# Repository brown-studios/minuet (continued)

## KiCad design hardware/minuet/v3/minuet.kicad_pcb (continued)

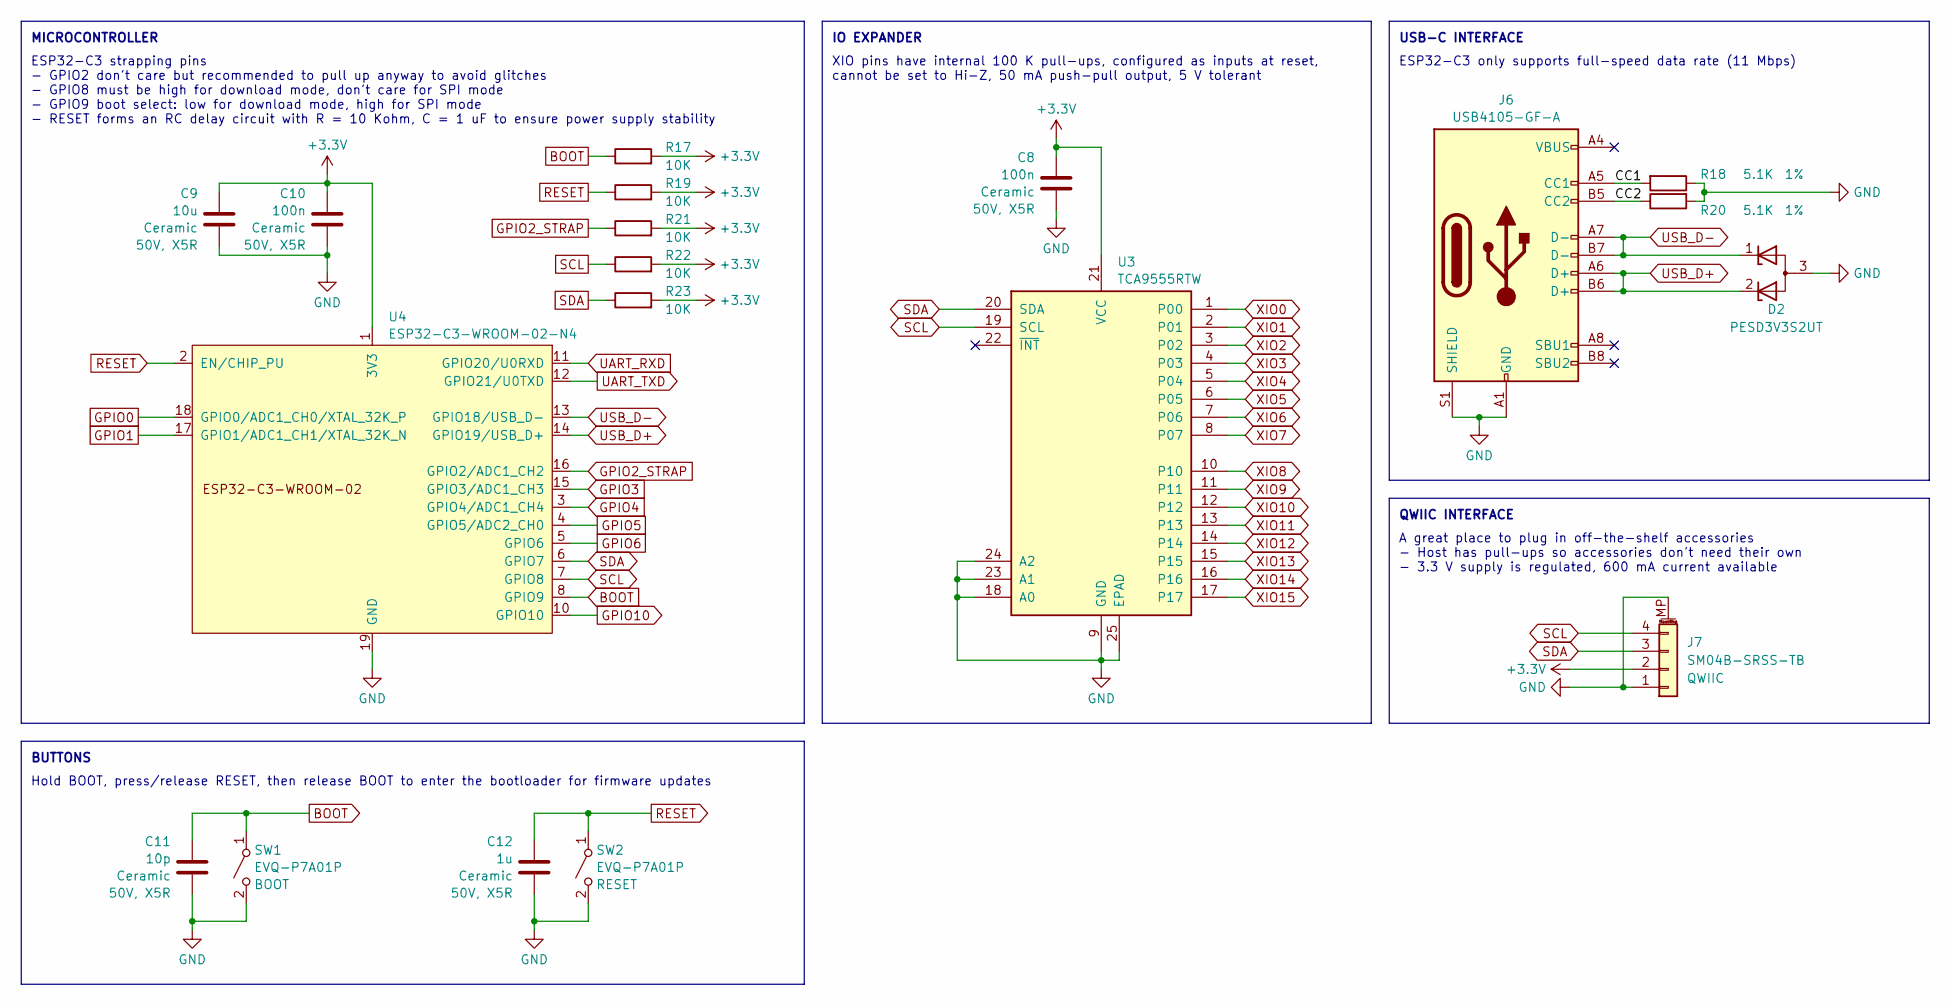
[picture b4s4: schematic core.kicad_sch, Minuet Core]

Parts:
C8, C10: 100n; C_0603_1608Metric; Rating 50V, X5R; LCSC C14663
C9: 10u; C_0805_2012Metric; Rating 50V, X5R; LCSC C15850
C11: 10p; C_0603_1608Metric; Rating 50V, X5R; LCSC C1634
C12: 1u; C_0603_1608Metric; Rating 50V, X5R; LCSC C15849
D2: PESD3V3S2UT; SOT-23; LCSC C84276
J6: USB4105-GF-A; USB_C_Receptacle_GCT_USB4105-xx-A_16P_TopMnt_Horizontal; LCSC C2988369
J7: SM04B-SRSS-TB; JST_SH_SM04B-SRSS-TB_1x04-1MP_P1.00mm_Horizontal; LCSC C160404
R17, R19, R21, R22, R23: 10K; R_0603_1608Metric; LCSC C25804
R18, R20: 5.1K; R_0603_1608Metric; Rating 1%; LCSC C23186
SW1, SW2: EVQ-P7A01P; SW_SPST_EVQP7A; LCSC C79167
U3: TCA9555RTW; WQFN-24-1EP_4x4mm_P0.5mm_EP2.45x2.45mm; LCSC C140277
U4: ESP32-C3-WROOM-02-N4; ESP32-C3-WROOM-02; LCSC C2934560

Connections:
+3.3V: C8.1, C9.2, C10.1, J7.2, R17.2, R19.2, R21.2, R22.2, R23.2, U3.21 (VCC), U4.1 (3V3); also elsewhere on the board
/core/CC1: J6.A5 (CC1), R18.2
/core/CC2: J6.B5 (CC2), R20.1
BOOT: C11.1, R17.1, SW1.1 (A), U4.8 (GPIO9); also elsewhere on the board
GND: C8.2, C9.1, C10.2, C11.2, C12.2, D2.3 (A), J6.A1 (GND), J6.A12 (GND), J6.B1 (GND), J6.B12 (GND), J6.S1 (SHIELD), J7.1, J7.MP (MountPin), R18.1, R20.2, SW1.2 (B), SW2.2 (B), U3.9 (GND), U3.18 (A0), U3.23 (A1), U3.24 (A2), U3.25 (EPAD), U4.9 (GND), U4.19 (GND); also elsewhere on the board
GPIO0: U4.18 (GPIO0/ADC1_CH0/XTAL_32K_P); also elsewhere on the board
GPIO1: U4.17 (GPIO1/ADC1_CH1/XTAL_32K_N); also elsewhere on the board
GPIO2_STRAP: R21.1, U4.16 (GPIO2/ADC1_CH2); also elsewhere on the board
GPIO3: U4.15 (GPIO3/ADC1_CH3); also elsewhere on the board
GPIO4: U4.3 (GPIO4/ADC1_CH4); also elsewhere on the board
GPIO5: U4.4 (GPIO5/ADC2_CH0); also elsewhere on the board
GPIO6: U4.5 (GPIO6); also elsewhere on the board
GPIO10: U4.10 (GPIO10); also elsewhere on the board
RESET: C12.1, R19.1, SW2.1 (A), U4.2 (EN/CHIP_PU); also elsewhere on the board
SCL: J7.4, R22.1, U3.19 (SCL), U4.7 (GPIO8); also elsewhere on the board
SDA: J7.3, R23.1, U3.20 (SDA), U4.6 (GPIO7); also elsewhere on the board
UART_RXD: U4.11 (GPIO20/U0RXD); also elsewhere on the board
UART_TXD: U4.12 (GPIO21/U0TXD); also elsewhere on the board
USB_D+: D2.2 (K), J6.A6 (D+), J6.B6 (D+), U4.14 (GPIO19/USB_D+)
USB_D-: D2.1 (K), J6.A7 (D-), J6.B7 (D-), U4.13 (GPIO18/USB_D-)
XIO0: U3.1 (P00); also elsewhere on the board
XIO1: U3.2 (P01); also elsewhere on the board
XIO2: U3.3 (P02); also elsewhere on the board
XIO3: U3.4 (P03); also elsewhere on the board
XIO4: U3.5 (P04); also elsewhere on the board
XIO5: U3.6 (P05); also elsewhere on the board
XIO6: U3.7 (P06); also elsewhere on the board
XIO7: U3.8 (P07); also elsewhere on the board
XIO8: U3.10; also elsewhere on the board
XIO9: U3.11; also elsewhere on the board
XIO10: U3.12; also elsewhere on the board
XIO11: U3.13; also elsewhere on the board
XIO12: U3.14; also elsewhere on the board
XIO13: U3.15; also elsewhere on the board
XIO14: U3.16; also elsewhere on the board
XIO15: U3.17; also elsewhere on the board

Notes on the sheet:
IO EXPANDER
USB-C INTERFACE
XIO pins have internal 100 K pull-ups, configured as inputs at reset, cannot be set to Hi-Z, 50 mA push-pull output, 5 V tolerant
ESP32-C3 strapping pins - GPIO2 don't care but recommended to pull up anyway to avoid glitches - GPIO8 must be high for download mode, don't care for SPI mode - GPIO9 boot select: low for download mode, high for SPI mode - RESET forms an RC delay circuit with R = 10 Kohm, C = 1 uF to ensure power s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
Hold BOOT, press/release RESET, then release BOOT to enter the bootloader for firmware updates
BUTTONS
ESP32-C3 only supports full-speed data rate (11 Mbps)
QWIIC INTERFACE
A great place to plug in off-the-shelf accessories - Host has pull-ups so accessories don't need their own - 3.3 V supply is regulated, 600 mA current available
MICROCONTROLLER

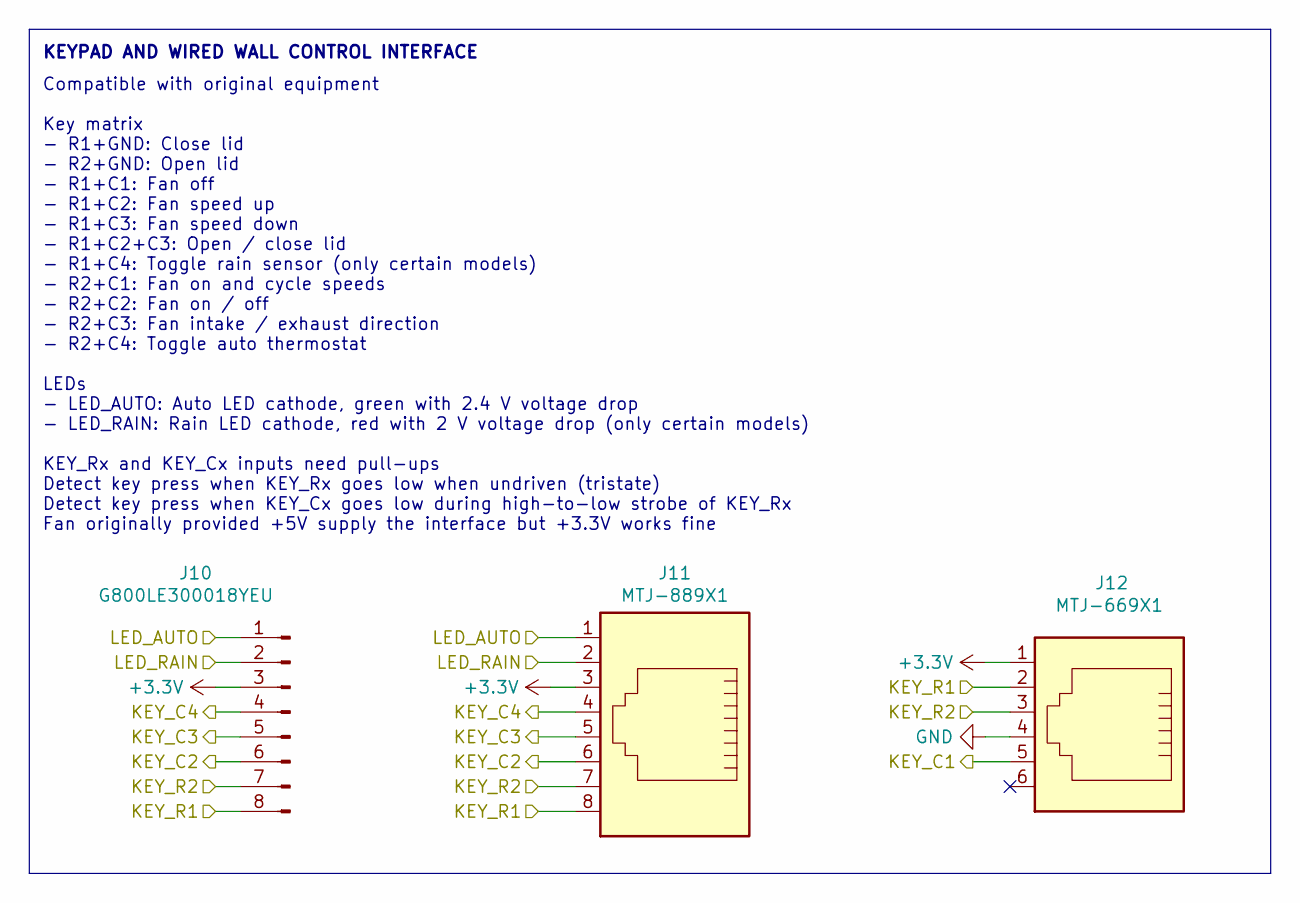
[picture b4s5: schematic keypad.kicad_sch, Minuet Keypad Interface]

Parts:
J10: G800LE300018YEU; PinHeader_1x08_P2.54mm_Vertical; LCSC C3345591
J11: MTJ-889X1; CONN_MTJ-889X1_ADM; LCSC C6105889
J12: MTJ-669X1; CONN_MTJ-669X1_ADM; LCSC C5785037

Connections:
+3.3V: J10.3, J11.3, J12.1; also elsewhere on the board
/keypad/LED_AUTO: J10.1, J11.1; also elsewhere on the board
/keypad/LED_RAIN: J10.2, J11.2; also elsewhere on the board
GND: J12.4; also elsewhere on the board
XIO2: J10.5, J11.5; also elsewhere on the board
XIO3: J10.7, J11.7, J12.3; also elsewhere on the board
XIO4: J10.6, J11.6; also elsewhere on the board
XIO5: J10.8, J11.8, J12.2; also elsewhere on the board
XIO6: J10.4, J11.4; also elsewhere on the board
XIO7: J12.5; also elsewhere on the board

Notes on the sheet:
Compatible with original equipment Key matrix - R1+GND: Close lid - R2+GND: Open lid - R1+C1: Fan off - R1+C2: Fan speed up - R1+C3: Fan speed down - R1+C2+C3: Open / close lid - R1+C4: Toggle rain sensor (only certain models) - R2+C1: Fan on and cycle speeds - R2+C2: Fan on / off - R2+C3: Fan inta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
KEYPAD AND WIRED WALL CONTROL INTERFACE

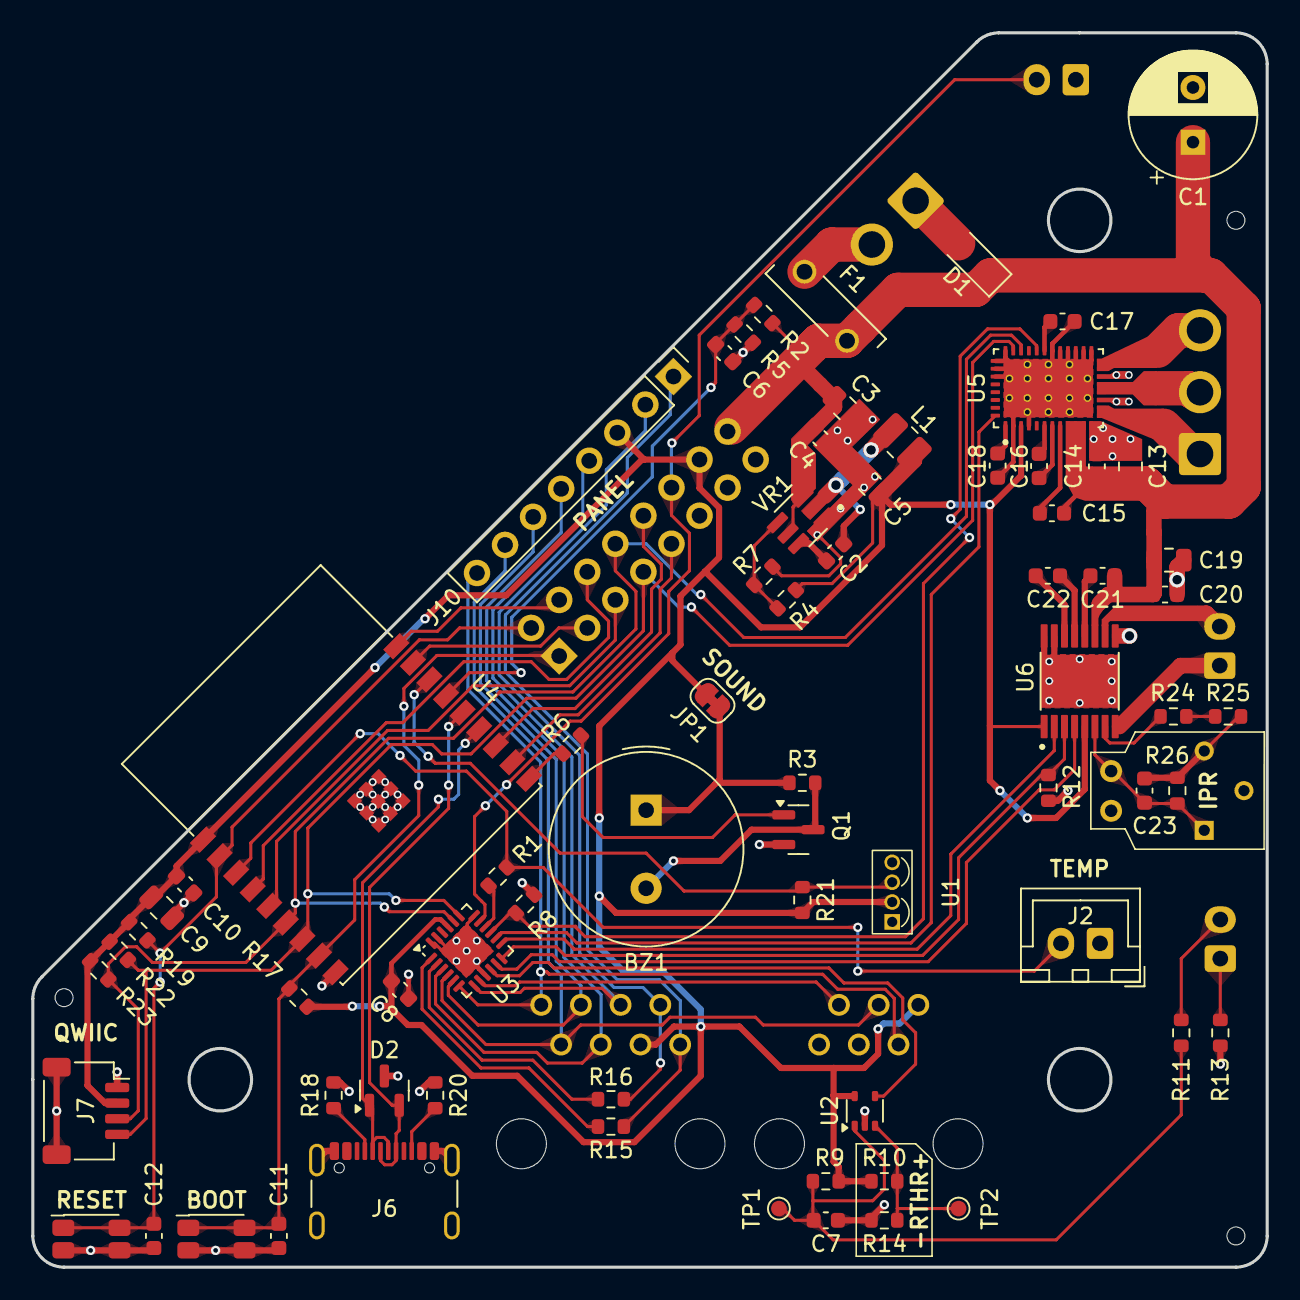
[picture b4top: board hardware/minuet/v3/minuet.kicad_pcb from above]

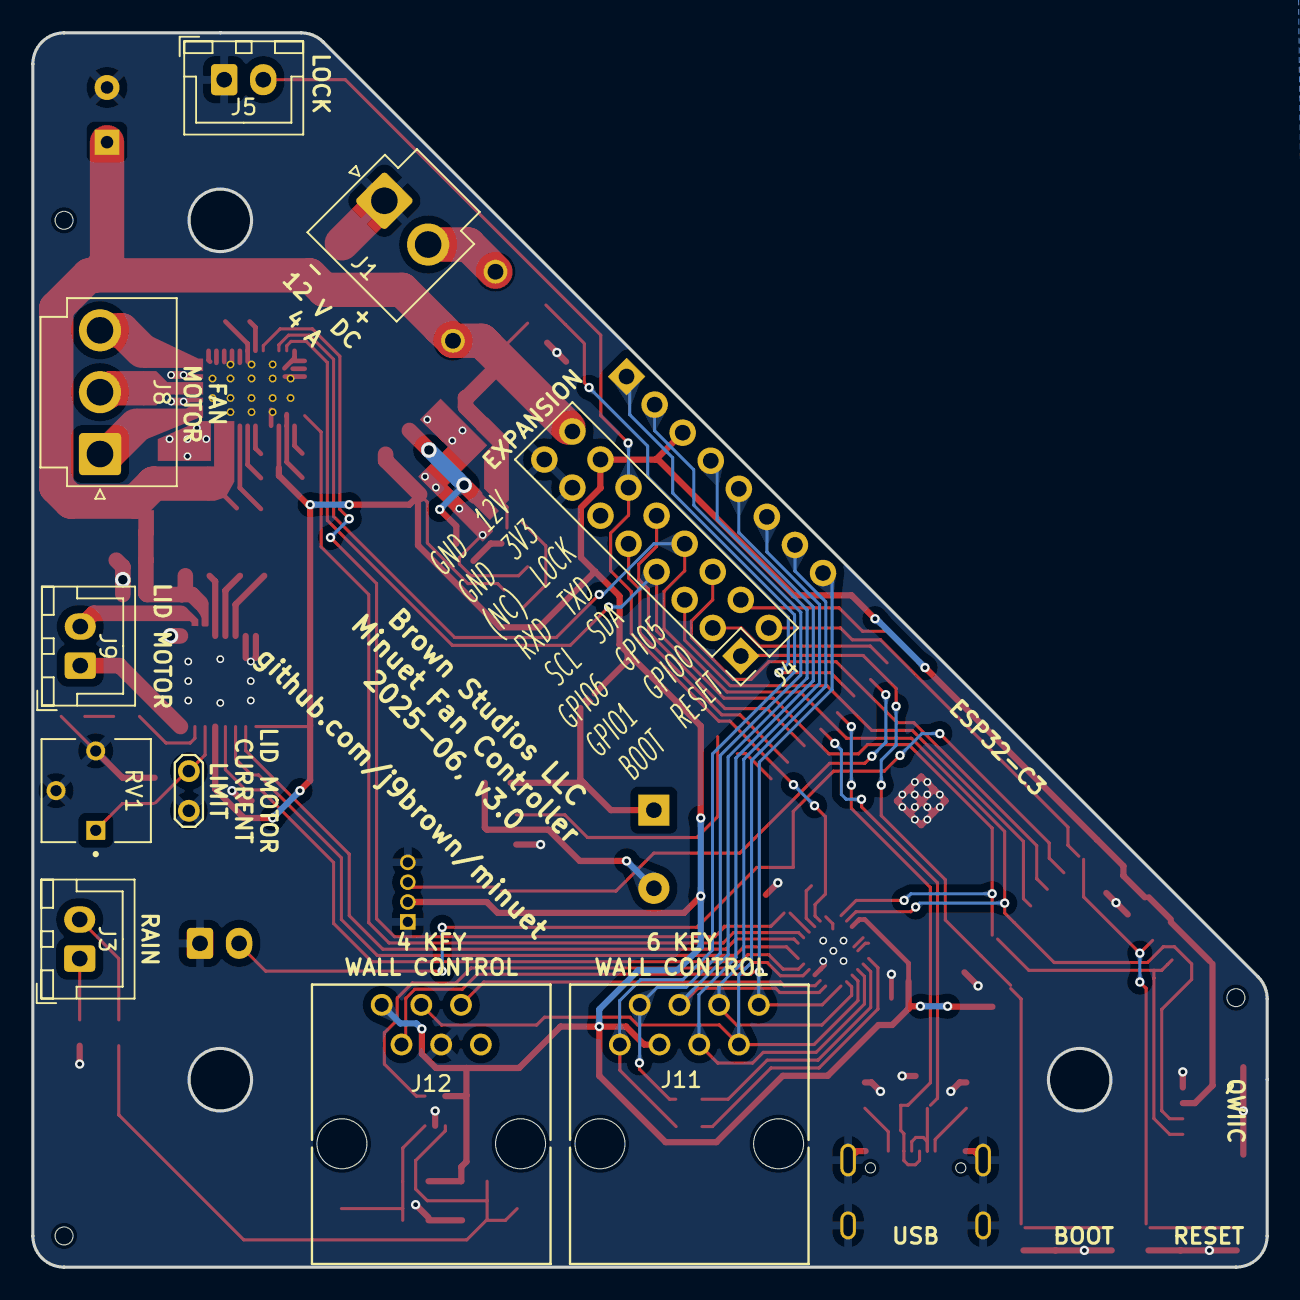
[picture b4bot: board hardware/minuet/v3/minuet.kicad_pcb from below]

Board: 2 copper layers, 79.0 x 79.0 mm, 88 parts (10 on the bottom side), 70 nets.

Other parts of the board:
TH1, TH2, TH3: JLCPCB_PCBA_Tooling_Hole

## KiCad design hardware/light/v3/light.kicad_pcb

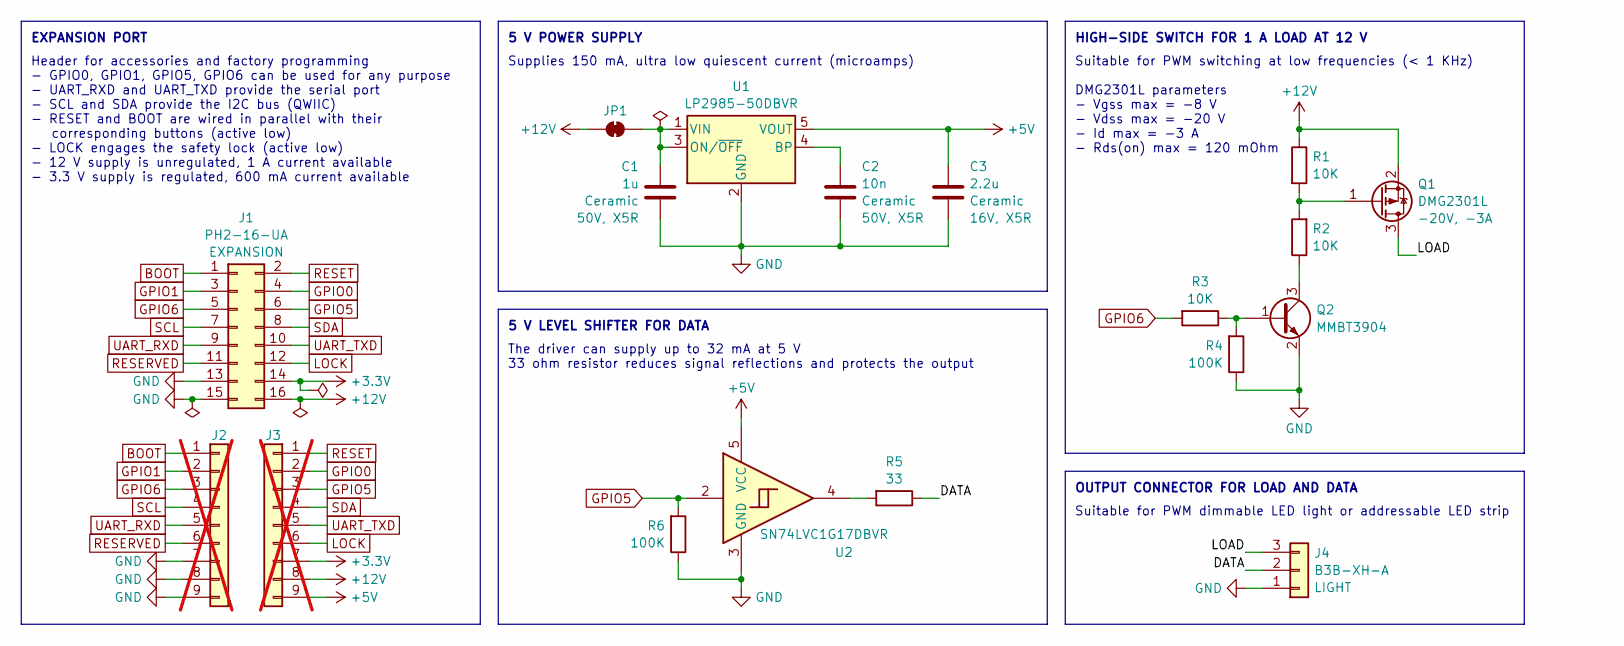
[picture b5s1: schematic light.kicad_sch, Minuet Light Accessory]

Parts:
C1: 1u; C_0603_1608Metric; Rating 50V, X5R; LCSC C15849
C2: 10n; C_0603_1608Metric; Rating 50V, X5R; LCSC C57112
C3: 2.2u; C_0603_1608Metric; Rating 16V, X5R; LCSC C23630
J1: PH2-16-UA; PinHeader_2x08_P2.54mm_Vertical; LCSC C492425
J2, J3: Conn_01x09; Pins_1x09; not fitted
J4: B3B-XH-A; JST_XH_B3B-XH-A_1x03_P2.50mm_Vertical; LCSC C144394
JP1: SolderJumper_2_Open; SolderJumper-2_P1.3mm_Bridged_RoundedPad1.0x1.5mm
Q1: DMG2301L; SOT-23; Rating -20V, -3A; LCSC C102619
Q2: MMBT3904; SOT-23; LCSC C20526
R1, R2, R3: 10K; R_0603_1608Metric; LCSC C25804
R4, R6: 100K; R_0603_1608Metric; LCSC C25803
R5: 33; R_0603_1608Metric; LCSC C23140
U1: LP2985-50DBVR; SOT-23-5; LCSC C74511
U2: SN74LVC1G17DBVR; SOT-23-5; LCSC C7836

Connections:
+3.3V: J1.14, J3.7
+5V: C3.2, J3.9, U1.5 (VOUT), U2.5 (VCC)
+12V: J1.16, J3.8, JP1.2 (B), Q1.2 (S), R1.1
/DATA: J4.2, R5.1
/LOAD: J4.3, Q1.3 (D)
BOOT: J1.1, J2.1
GND: C1.2, C2.1, C3.1, J1.13, J1.15, J2.7, J2.8, J2.9, J4.1, Q2.2 (E), R4.1, R6.1, U1.2 (GND), U2.3 (GND)
GPIO0: J1.4, J3.2
GPIO1: J1.3, J2.2
GPIO5: J1.6, J3.3, R6.2, U2.2
GPIO6: J1.5, J2.3, R3.2
LOCK: J1.12, J3.6
unnamed: C1.1, JP1.1 (A), U1.1 (VIN), U1.3 (ON/~OFF)
unnamed: Q1.1 (G), R1.2, R2.2
unnamed: Q2.1 (B), R3.1, R4.2
unnamed: Q2.3 (C), R2.1
unnamed: R5.2, U2.4
unnamed: C2.2, U1.4 (BP)
RESERVED: J1.11, J2.6
RESET: J1.2, J3.1
SCL: J1.7, J2.4
SDA: J1.8, J3.4
UART_RXD: J1.9, J2.5
UART_TXD: J1.10, J3.5

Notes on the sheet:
HIGH-SIDE SWITCH FOR 1 A LOAD AT 12 V
Suitable for PWM switching at low frequencies (< 1 KHz) DMG2301L parameters - Vgss max = -8 V - Vdss max = -20 V - Id max = -3 A - Rds(on) max = 120 mOhm
The driver can supply up to 32 mA at 5 V 33 ohm resistor reduces signal reflections and protects the output
5 V LEVEL SHIFTER FOR DATA
EXPANSION PORT
Header for accessories and factory programming - GPIO0, GPIO1, GPIO5, GPIO6 can be used for any purpose - UART_RXD and UART_TXD provide the serial port - SCL and SDA provide the I2C bus (QWIIC) - RESET and BOOT are wired in parallel with their corresponding buttons (active low) - LOCK engages the s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
Suitable for PWM dimmable LED light or addressable LED strip
Supplies 150 mA, ultra low quiescent current (microamps)
5 V POWER SUPPLY
OUTPUT CONNECTOR FOR LOAD AND DATA

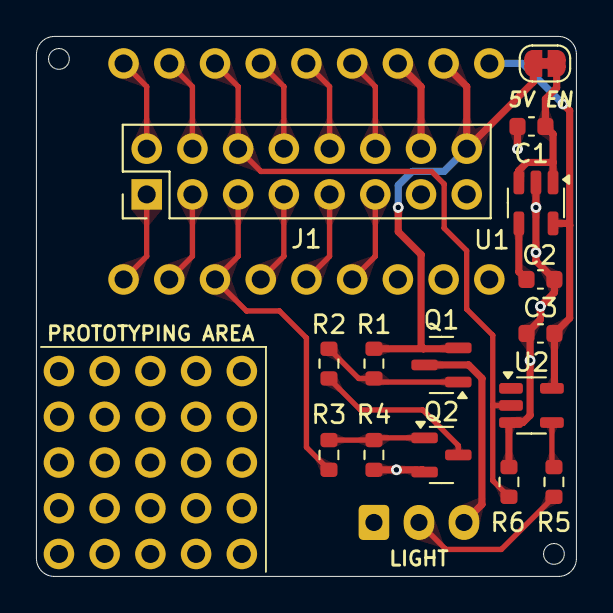
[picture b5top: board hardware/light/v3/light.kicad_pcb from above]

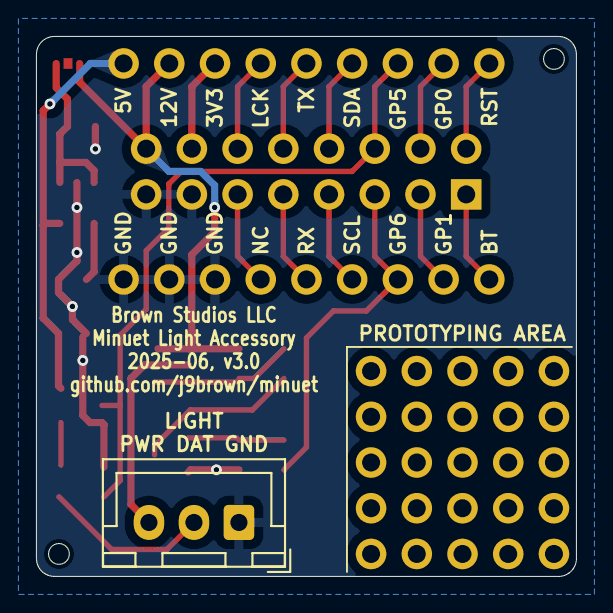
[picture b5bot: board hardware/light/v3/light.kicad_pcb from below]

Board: 2 copper layers, 30.0 x 30.0 mm, 21 parts (3 on the bottom side), 24 nets.

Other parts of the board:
PROTO: Val**; ProtoPins
TH1, TH2: JLCPCB_PCBA_Tooling_Hole

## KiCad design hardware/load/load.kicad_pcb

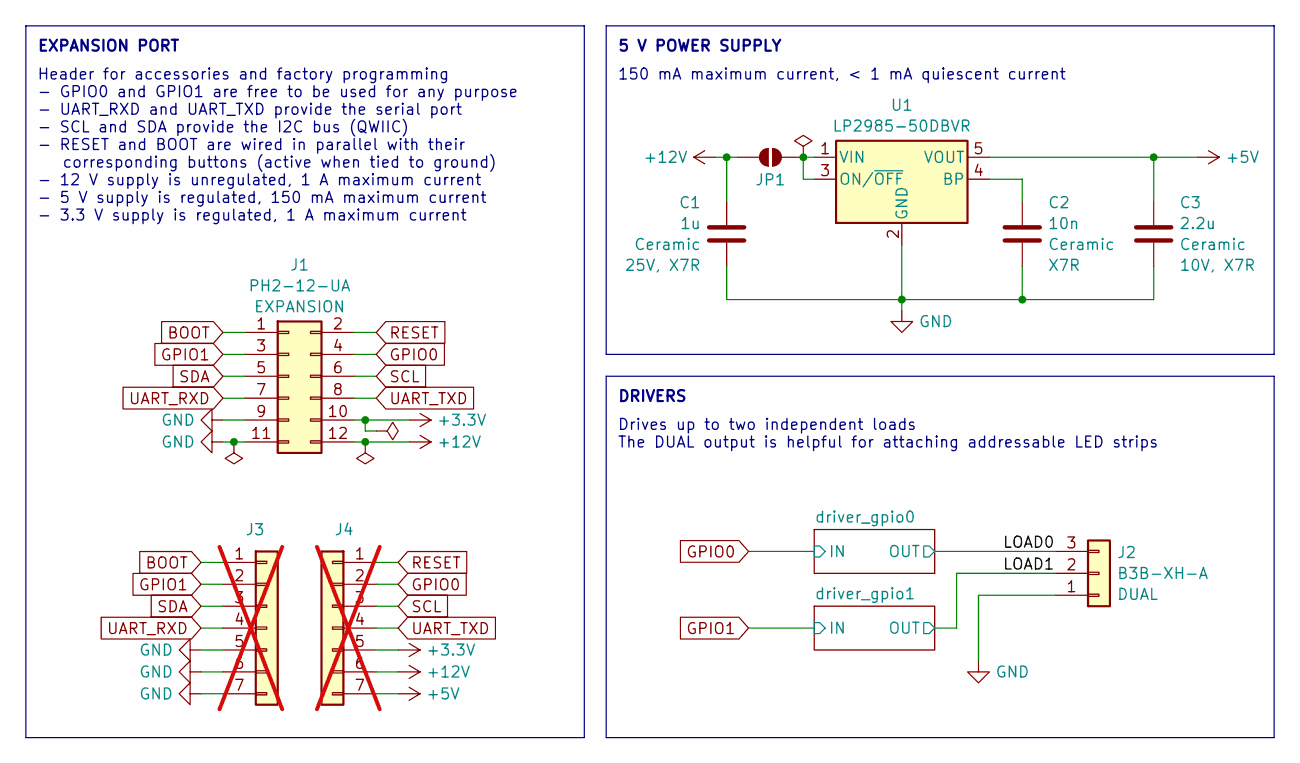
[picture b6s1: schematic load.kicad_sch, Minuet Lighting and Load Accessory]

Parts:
C1: 1u; C_0603_1608Metric_Pad1.08x0.95mm_HandSolder; Rating 25V, X7R
C2: 10n; C_0603_1608Metric_Pad1.08x0.95mm_HandSolder; Rating X7R
C3: 2.2u; C_0603_1608Metric_Pad1.08x0.95mm_HandSolder; Rating 10V, X7R
J1: PH2-12-UA; PinHeader_2x06_P2.54mm_Vertical
J2: B3B-XH-A; JST_XH_B3B-XH-A_1x03_P2.50mm_Vertical
J3, J4: Conn_01x07; Pins_1x07; not fitted
JP1: SolderJumper_2_Open; SolderJumper-2_P1.3mm_Open_TrianglePad1.0x1.5mm
U1: LP2985-50DBVR; SOT-23-5_HandSoldering

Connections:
+3.3V: J1.10, J4.5; also elsewhere on the board
+5V: C3.2, J4.7, U1.5 (VOUT); also elsewhere on the board
+12V: C1.1, J1.12, J4.6, JP1.1 (A); also elsewhere on the board
/LOAD0: J2.3; also elsewhere on the board
/LOAD1: J2.2; also elsewhere on the board
BOOT: J1.1, J3.1
GND: C1.2, C2.1, C3.1, J1.9, J1.11, J2.1, J3.5, J3.6, J3.7, U1.2 (GND); also elsewhere on the board
GPIO0: J1.4, J4.2; also elsewhere on the board
GPIO1: J1.3, J3.2; also elsewhere on the board
unnamed: JP1.2 (B), U1.1 (VIN), U1.3 (ON/~OFF)
unnamed: C2.2, U1.4 (BP)
RESET: J1.2, J4.1
SCL: J1.6, J4.3
SDA: J1.5, J3.3
UART_RXD: J1.7, J3.4
UART_TXD: J1.8, J4.4

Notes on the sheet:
Drives up to two independent loads The DUAL output is helpful for attaching addressable LED strips
EXPANSION PORT
DRIVERS
Header for accessories and factory programming - GPIO0 and GPIO1 are free to be used for any purpose - UART_RXD and UART_TXD provide the serial port - SCL and SDA provide the I2C bus (QWIIC) - RESET and BOOT are wired in parallel with their corresponding buttons (active when tied to ground) - 12 V 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
150 mA maximum current, < 1 mA quiescent current
5 V POWER SUPPLY

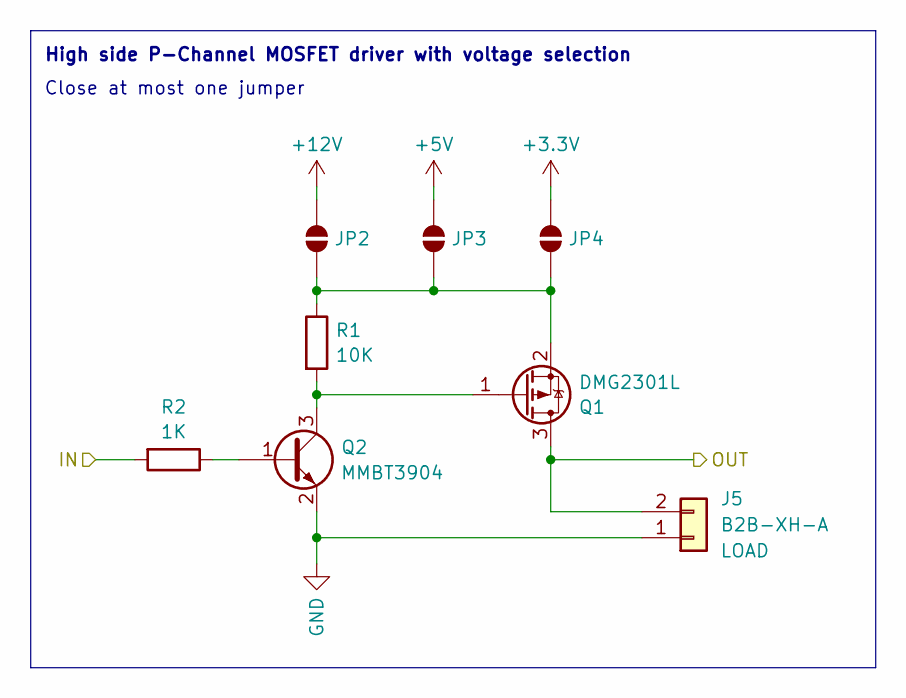
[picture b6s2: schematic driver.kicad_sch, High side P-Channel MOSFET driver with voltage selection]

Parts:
J5: B2B-XH-A; JST_XH_B2B-XH-A_1x02_P2.50mm_Vertical
JP2, JP3, JP4: SolderJumper_2_Open; SolderJumper-2_P1.3mm_Open_TrianglePad1.0x1.5mm
Q1: DMG2301L; SOT-23_Handsoldering
Q2: MMBT3904; SOT-23_Handsoldering
R1: 10K; R_0603_1608Metric_Pad0.98x0.95mm_HandSolder
R2: 1K; R_0603_1608Metric_Pad0.98x0.95mm_HandSolder

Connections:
+3.3V: JP4.1 (A); also elsewhere on the board
+5V: JP3.1 (A); also elsewhere on the board
+12V: JP2.1 (A); also elsewhere on the board
/LOAD0: J5.2, Q1.3 (D); also elsewhere on the board
GND: J5.1, Q2.2 (E); also elsewhere on the board
GPIO0: R2.2; also elsewhere on the board
unnamed: JP2.2 (B), JP3.2 (B), JP4.2 (B), Q1.2 (S), R1.1
unnamed: Q1.1 (G), Q2.3 (C), R1.2
unnamed: Q2.1 (B), R2.1

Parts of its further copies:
J6: B2B-XH-A; JST_XH_B2B-XH-A_1x02_P2.50mm_Vertical
JP5, JP6, JP7: SolderJumper_2_Open; SolderJumper-2_P1.3mm_Open_TrianglePad1.0x1.5mm
Q3: DMG2301L; SOT-23_Handsoldering
Q4: MMBT3904; SOT-23_Handsoldering
R3: 10K; R_0603_1608Metric_Pad0.98x0.95mm_HandSolder
R4: 1K; R_0603_1608Metric_Pad0.98x0.95mm_HandSolder

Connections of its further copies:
+3.3V: JP7.1 (A); also elsewhere on the board
+5V: JP6.1 (A); also elsewhere on the board
+12V: JP5.1 (A); also elsewhere on the board
/LOAD1: J6.2, Q3.3 (D); also elsewhere on the board
GND: J6.1, Q4.2 (E); also elsewhere on the board
GPIO1: R4.2; also elsewhere on the board
unnamed: JP5.2 (B), JP6.2 (B), JP7.2 (B), Q3.2 (S), R3.1
unnamed: Q3.1 (G), Q4.3 (C), R3.2
unnamed: Q4.1 (B), R4.1

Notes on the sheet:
High side P-Channel MOSFET driver with voltage selection
Close at most one jumper

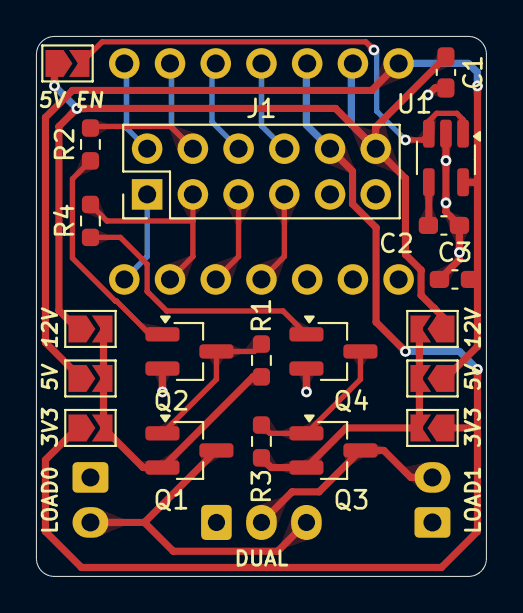
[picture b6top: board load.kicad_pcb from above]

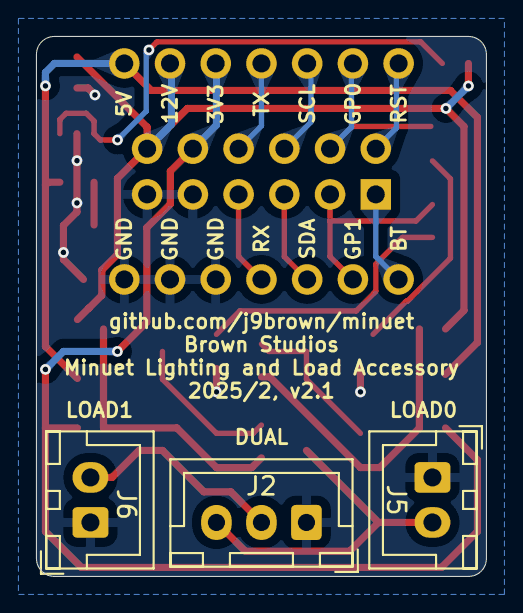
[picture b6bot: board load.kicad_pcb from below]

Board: 2 copper layers, 25.0 x 30.0 mm, 25 parts (5 on the bottom side), 22 nets.
